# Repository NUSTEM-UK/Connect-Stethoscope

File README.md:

# Connect-Stethoscope
 Direct servo control from a Pico with display board

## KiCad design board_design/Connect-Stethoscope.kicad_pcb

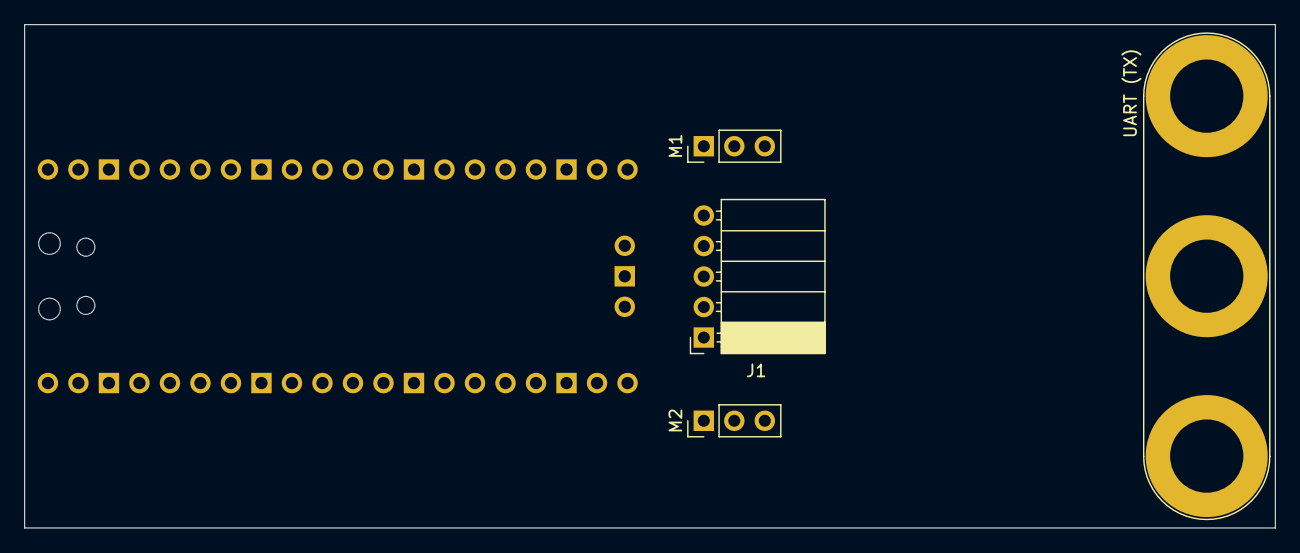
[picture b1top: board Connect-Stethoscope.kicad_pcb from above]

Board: 2 copper layers, 104.1 x 41.9 mm, 5 parts (1 on the bottom side), 10 nets, no tracks yet.

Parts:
J1: Conn_01x05; PinSocket_1x05_P2.54mm_Horizontal
M1, M2: Motor_Servo; PinHeader_1x03_P2.54mm_Vertical
U1: Pico; RPi_Pico_SMD_TH
UART (TX): Conn_01x03; Banana_Jack_3Pin

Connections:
+3V3: J1.2, U1.36 (3V3)
GND: J1.1, M1.3 (-), M2.3 (-), U1.3 (GND), U1.8 (GND), U1.13 (GND), U1.18 (GND), U1.23 (GND), U1.28 (GND), U1.38 (GND), UART (TX).2
unnamed: J1.3, U1.31 (GPIO26_ADC0)
unnamed: J1.4, U1.29 (GPIO22)
unnamed: J1.5, U1.27 (GPIO21)
unnamed: M1.1 (PWM), U1.4 (GPIO2)
unnamed: M2.1 (PWM), U1.5 (GPIO3)
unnamed: U1.11 (GPIO8), UART (TX).3
unnamed: U1.12 (GPIO9), UART (TX).1
VBUS: M1.2 (+), M2.2 (+), U1.40 (VBUS)

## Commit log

2022-03-15 Initial commit: first working version
2022-03-16 Simple stethoscope
2022-03-17 Single stethoscope
2022-03-17 Progress. Untested, but progress
2022-03-17 When MVC goes bad
2022-03-23 Progress, but not yet working
2022-03-23 Remove debug code
2022-03-23 PinButtonController kludge
2022-03-23 Pretty much working, as a draft
2022-03-23 WORKING!
2022-03-23 Copy steth-single to main.py
2022-05-12 Starting to learn KiCad
2022-06-06 Unsuccessful attempt to set application start mode
2022-06-06 Fix application state at startup
2022-06-07 Wiring diagrams
2022-06-07 Meh, backups
2023-03-23 Initial triage
2023-03-23 More triage
2023-03-25 PicoWGo setup
2023-03-25 Initial port to PicoGraphics and Button
2023-03-25 Comment updates
2023-03-28 Fixed up button rewrites
2023-03-28 Prep for merge to main
2025-07-17 Refactored servo_controller to own file
2025-07-17 Base on EasedServo rather than Servo class. Woop!
2026-05-22 Revision for square-wave sloshing.
